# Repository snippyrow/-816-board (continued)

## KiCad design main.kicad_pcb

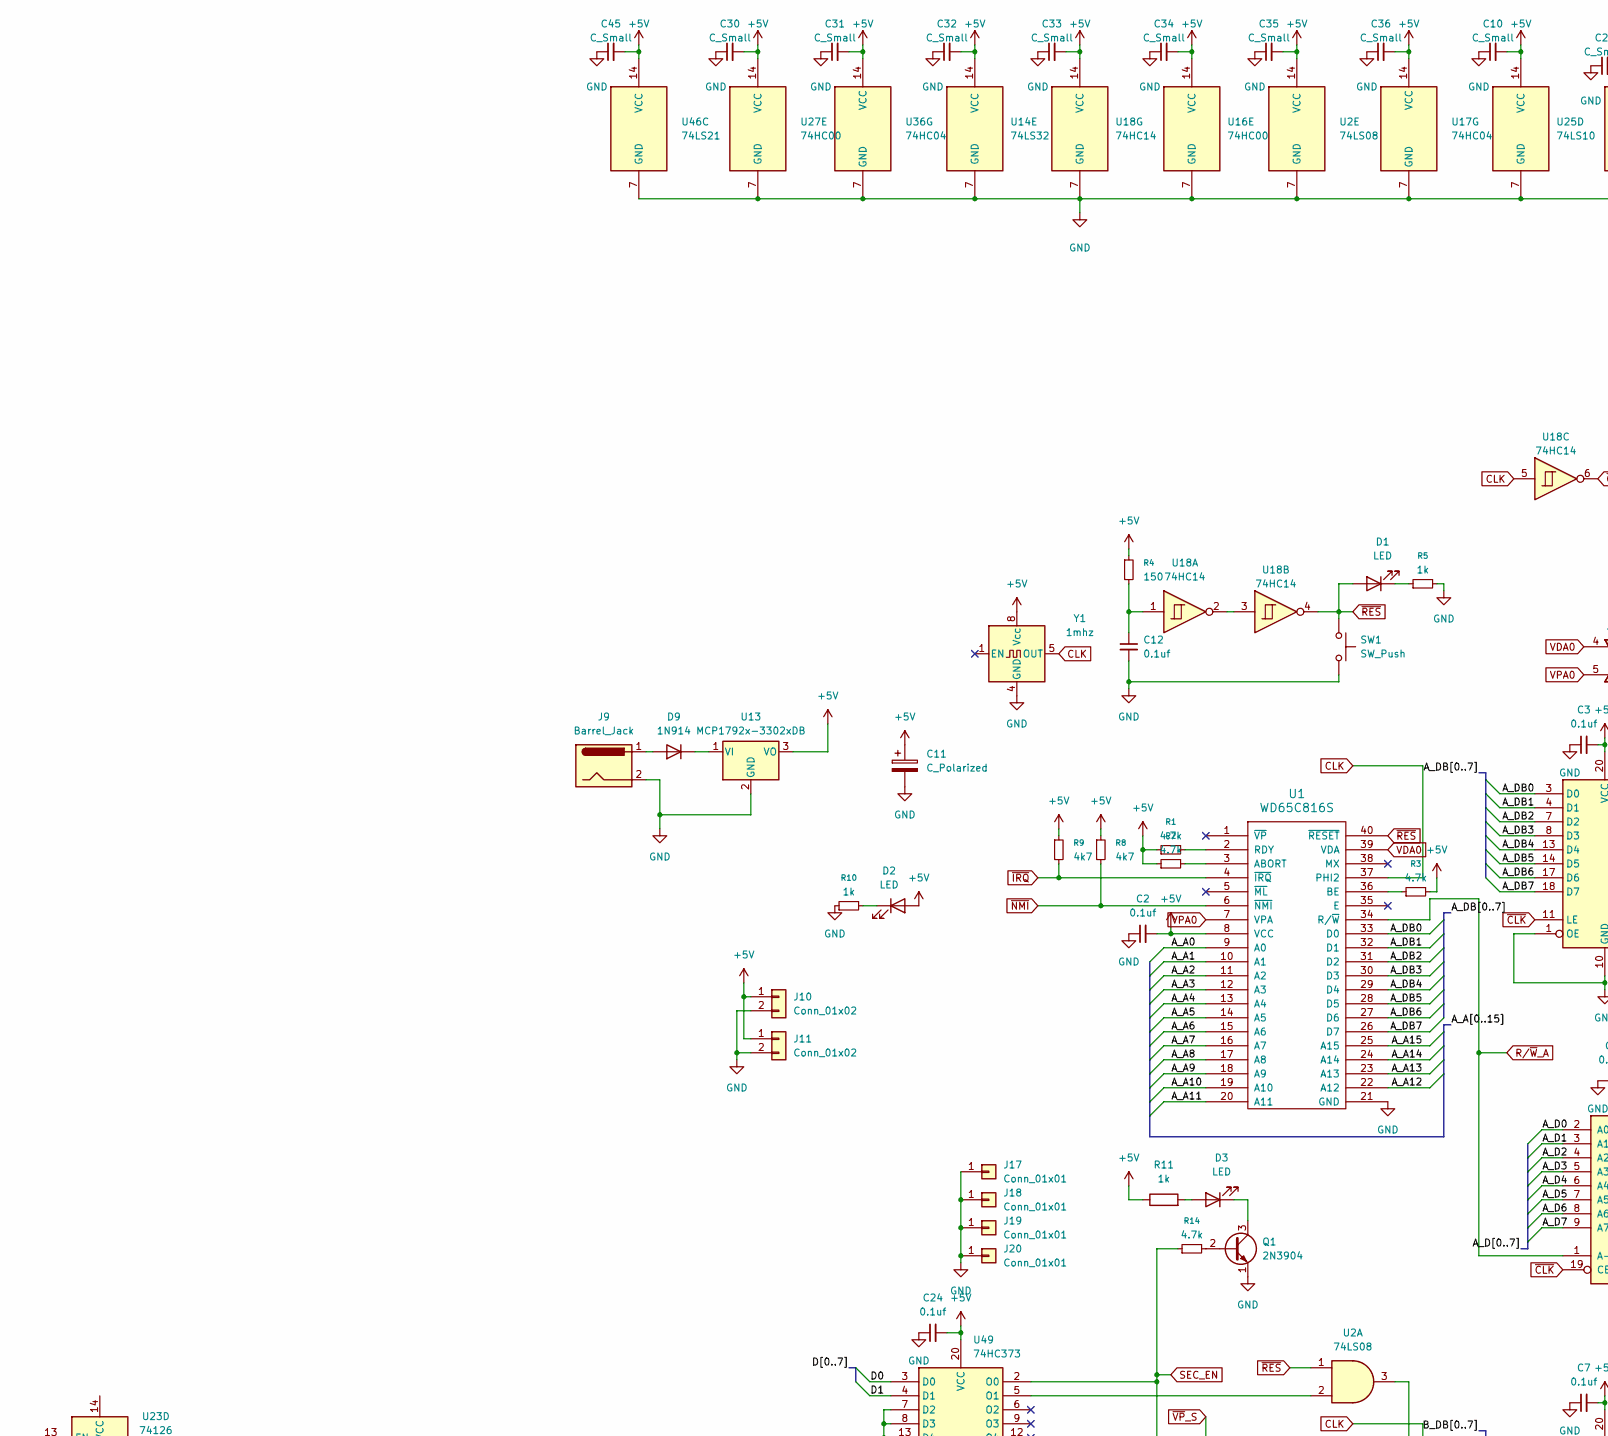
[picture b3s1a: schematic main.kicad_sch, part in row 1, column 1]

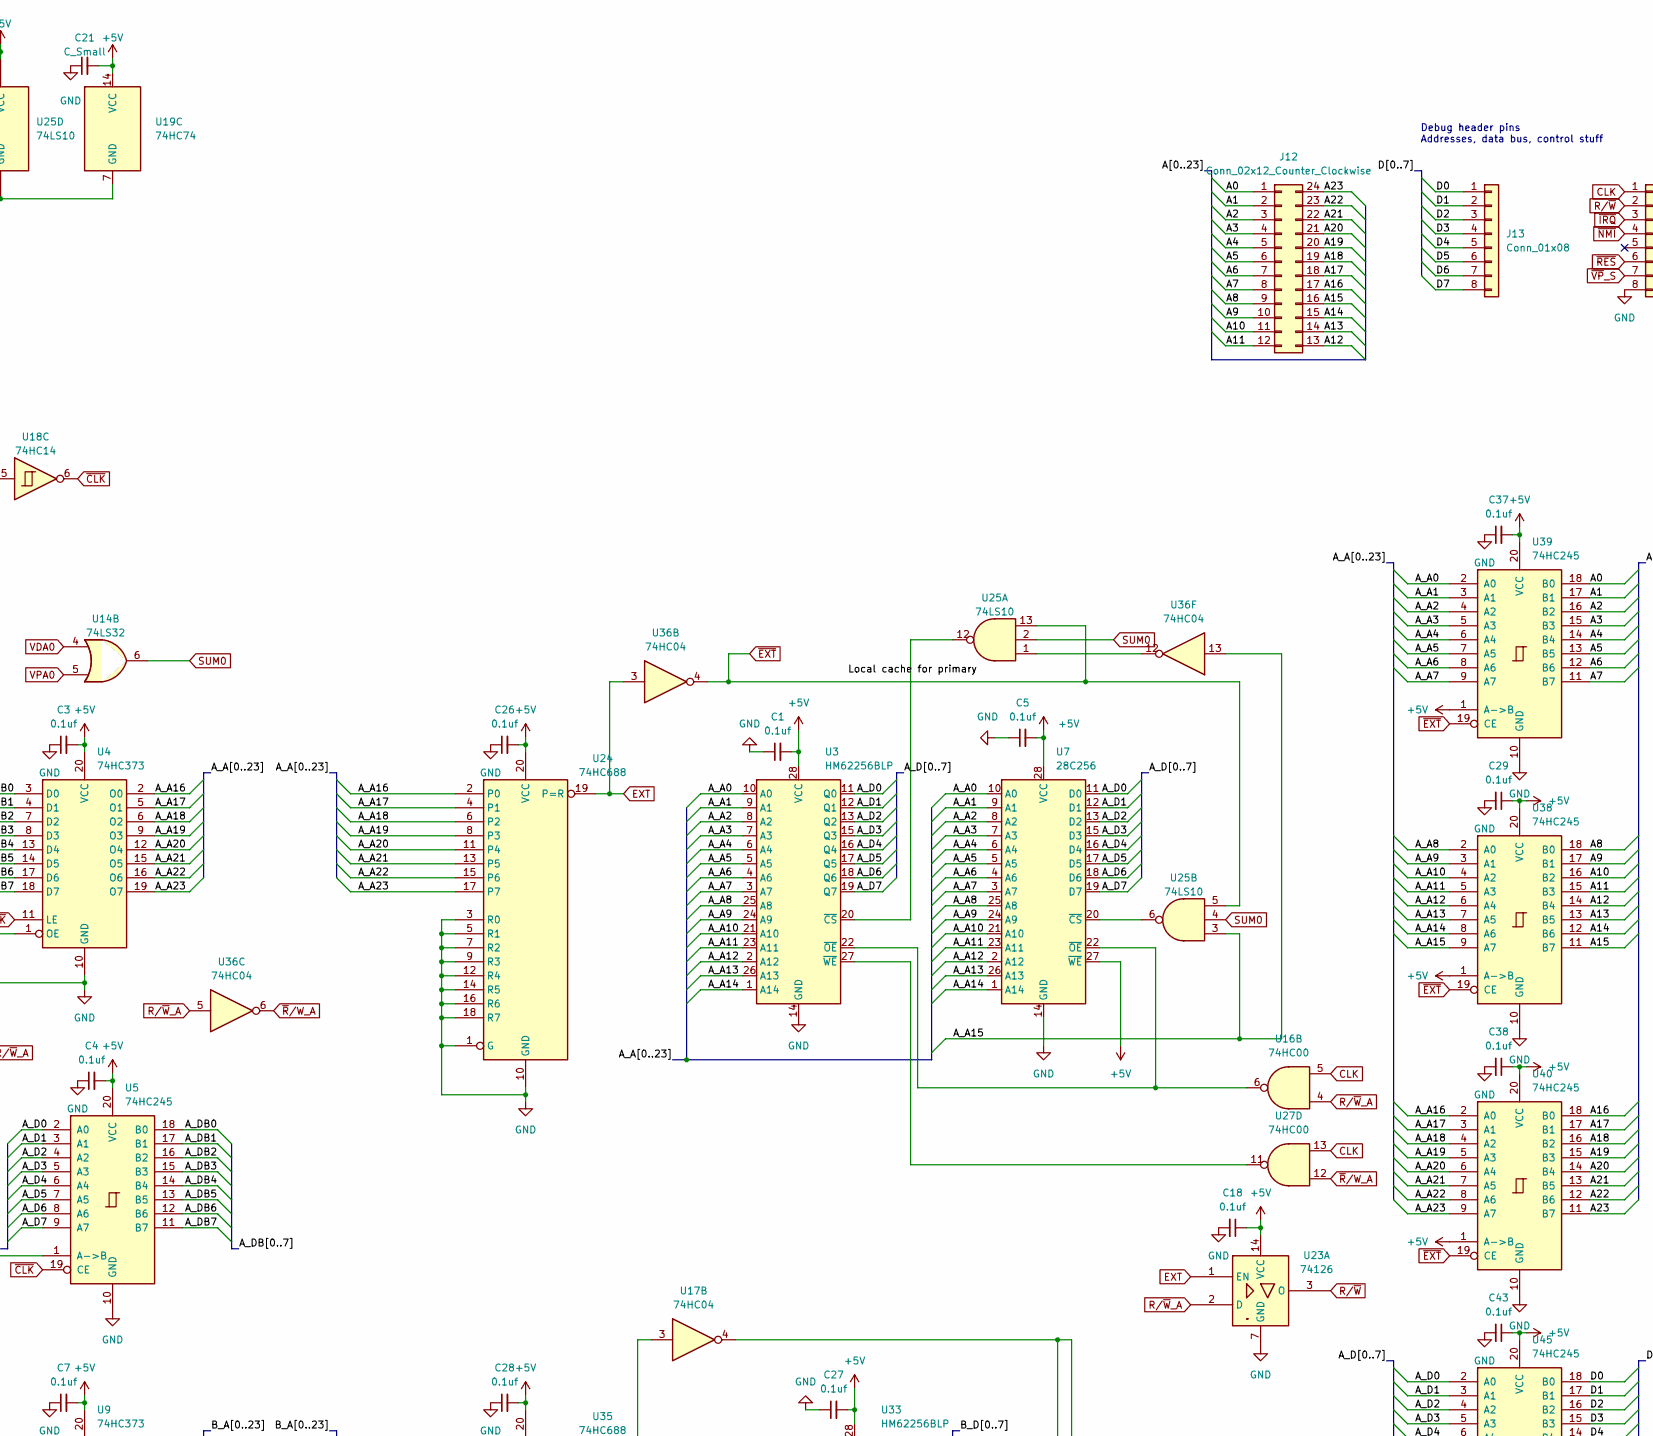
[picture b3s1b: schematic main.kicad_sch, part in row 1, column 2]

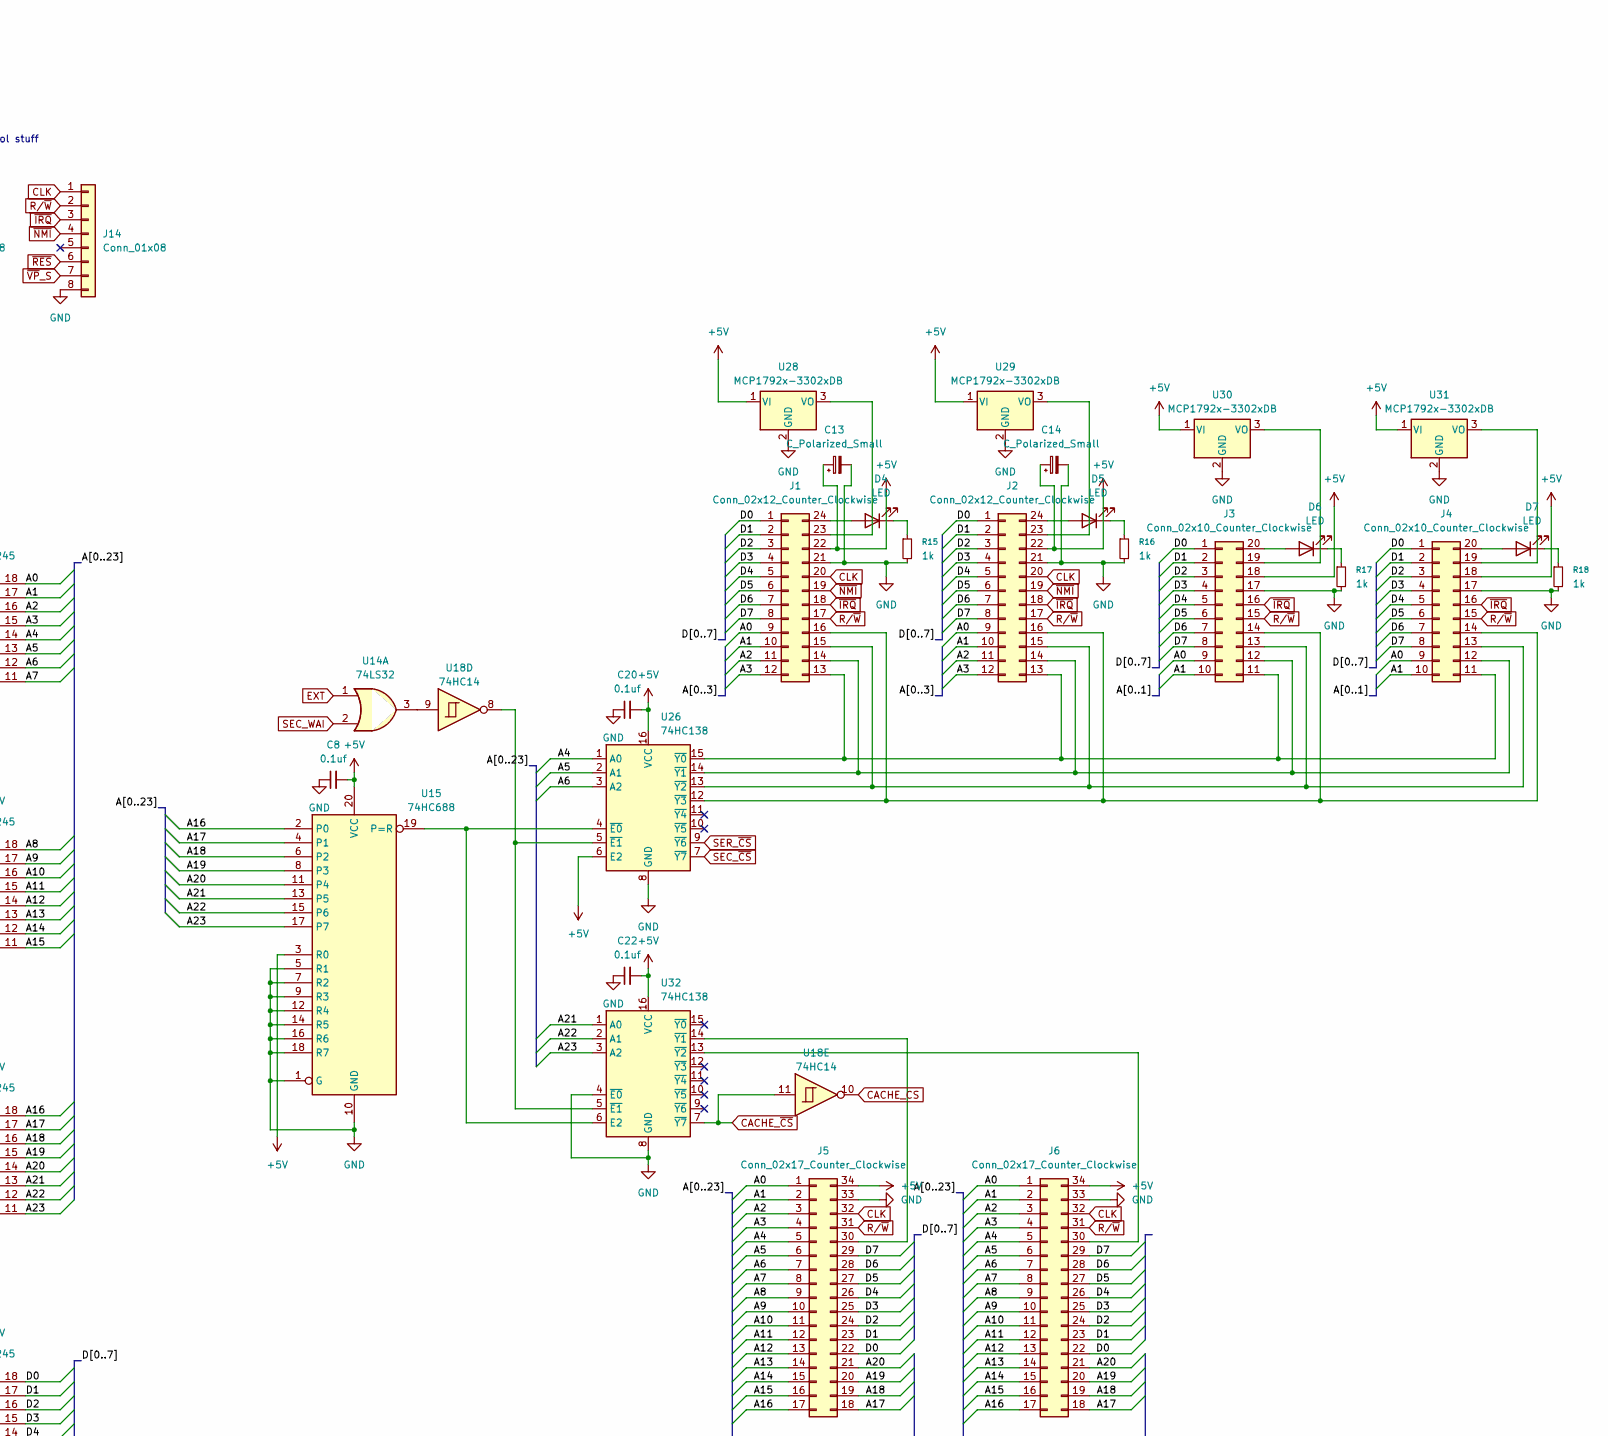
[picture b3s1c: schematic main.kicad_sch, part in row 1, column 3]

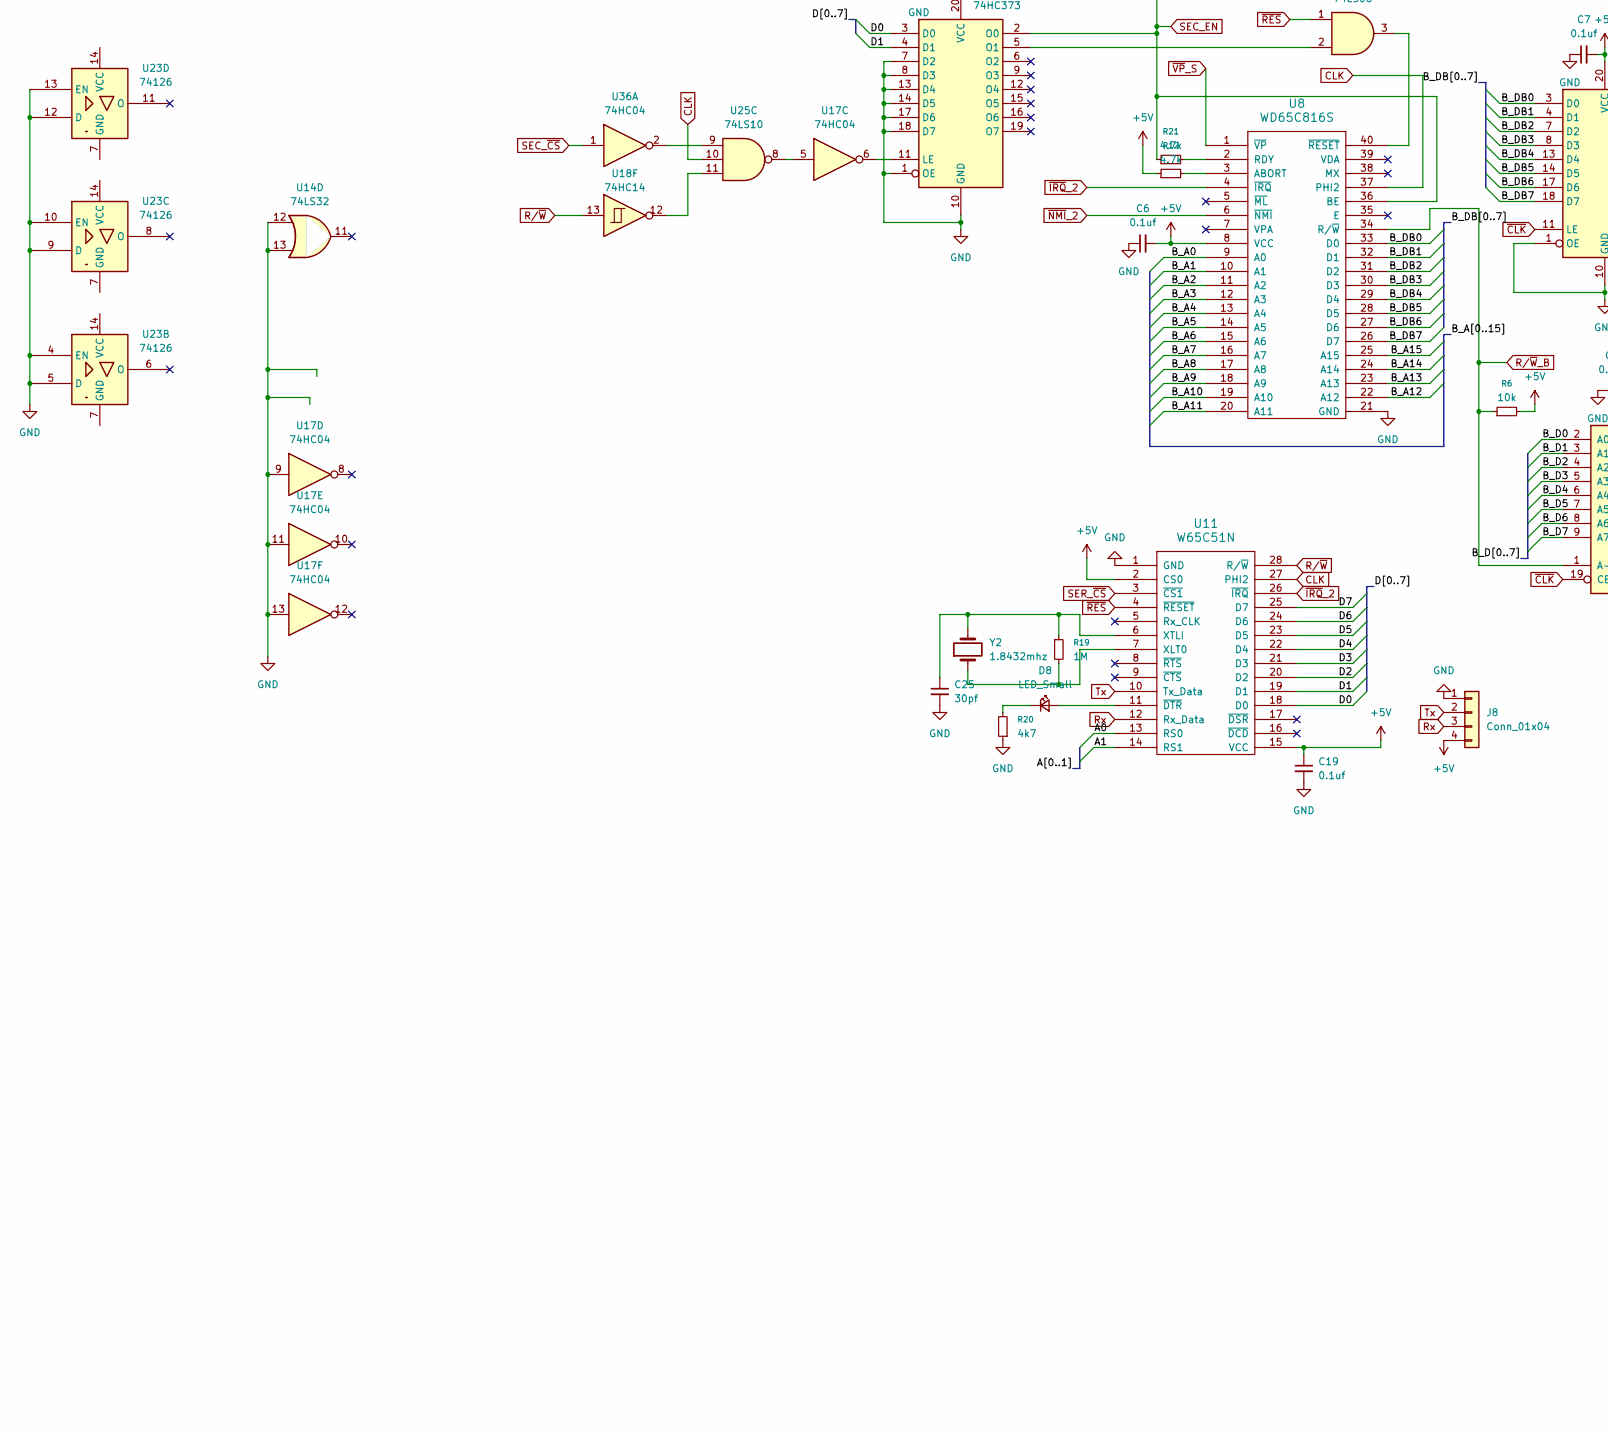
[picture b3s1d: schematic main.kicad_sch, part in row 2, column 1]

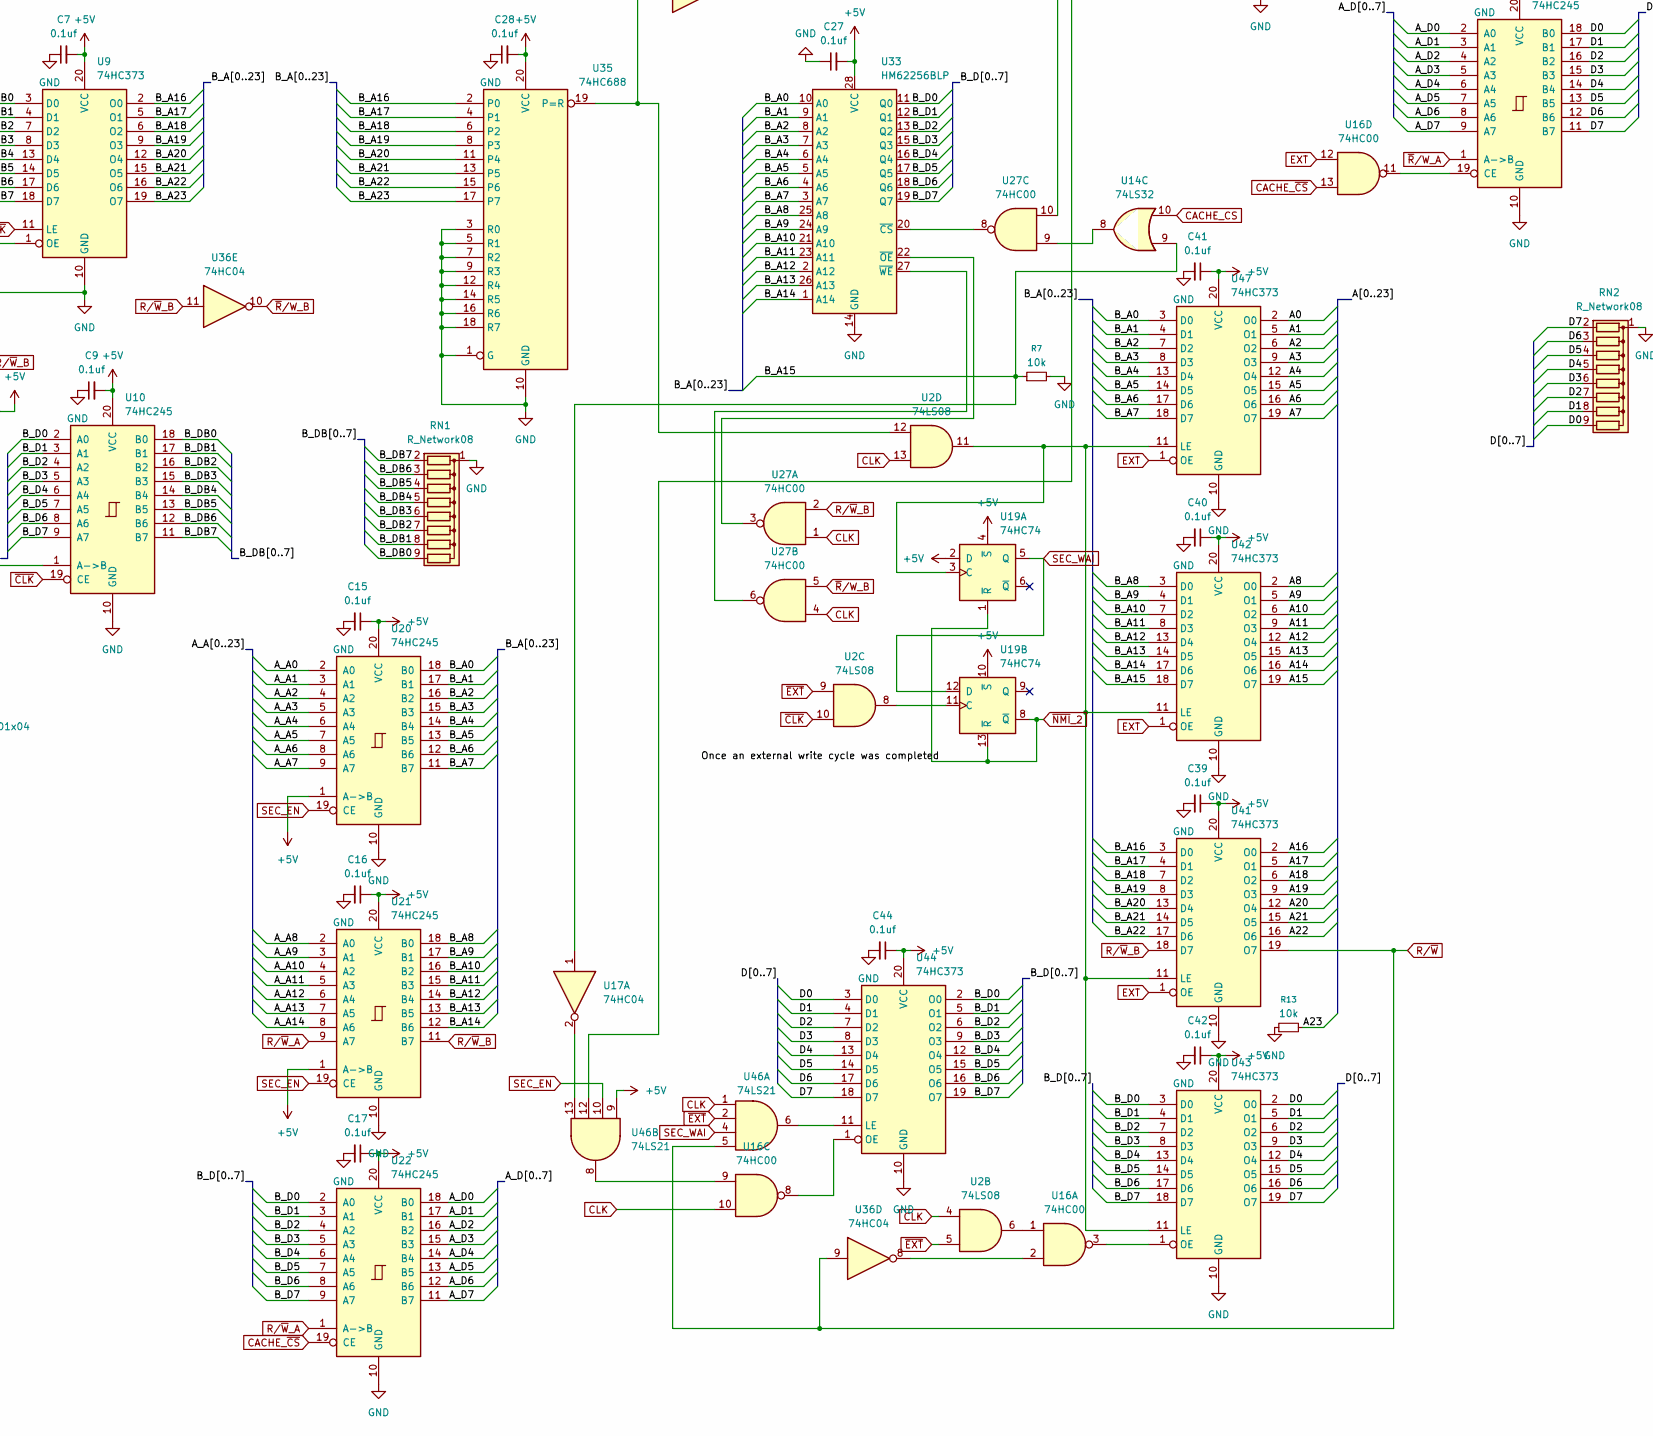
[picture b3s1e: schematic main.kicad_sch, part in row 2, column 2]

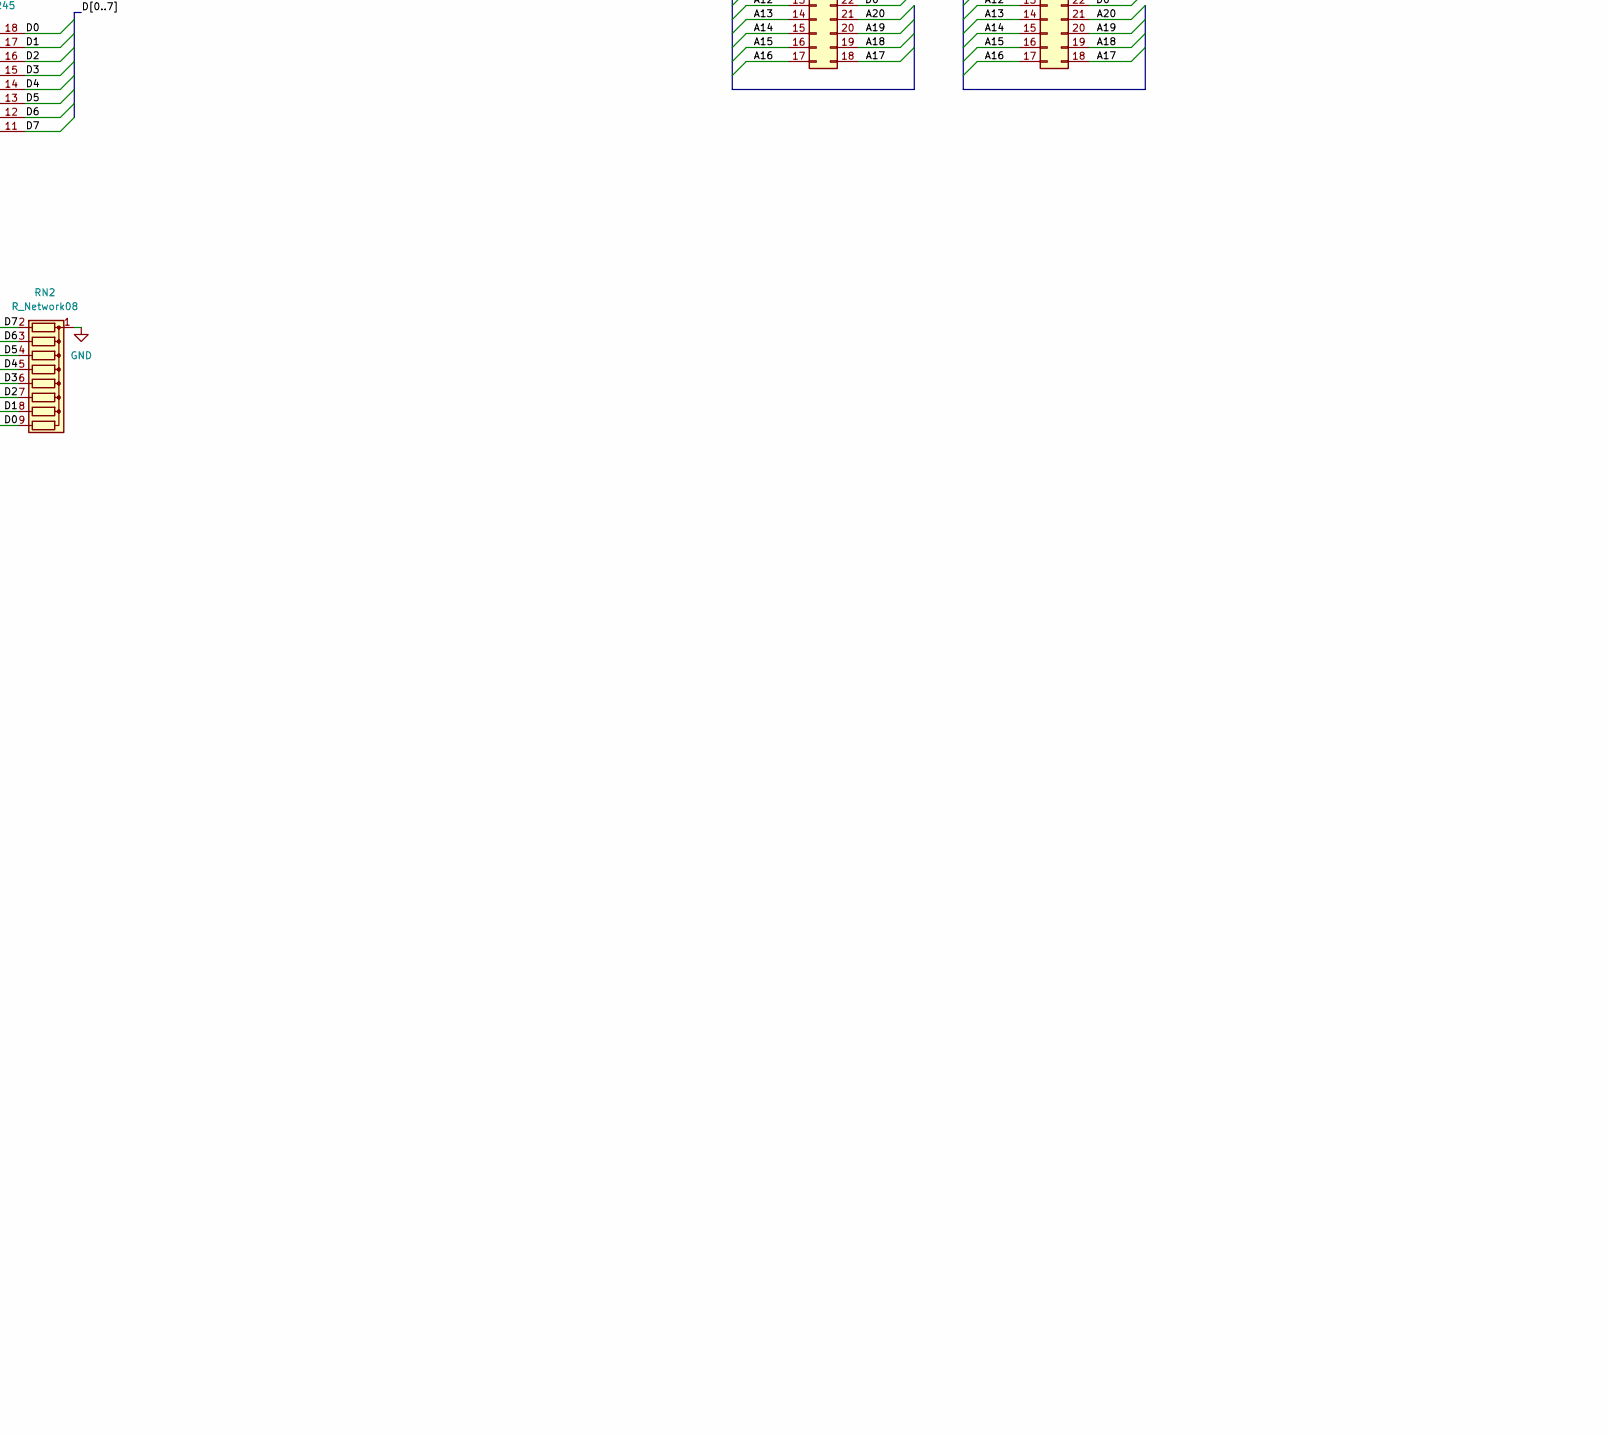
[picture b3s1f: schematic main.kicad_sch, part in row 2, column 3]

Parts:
C1, C2, C3, C4, C5, C6, C7, C8, C9, C12, C15, C16, C17, C18, C19, C20, C22, C24, C26, C27, C28, C29, C37, C38, C39, C40, C41, C42, C43, C44: 0.1uf; C_1206_3216Metric
C10, C21, C30, C31, C32, C33, C34, C35, C36, C45: C_Small; C_1206_3216Metric
C11: C_Polarized; CP_Radial_D10.0mm_P3.50mm
C13, C14: C_Polarized_Small; CP_Radial_D5.0mm_P2.00mm
C25: 30pf; C_Disc_D3.0mm_W2.0mm_P2.50mm
D1, D2, D3: LED; LED_D3.0mm
D4, D5, D6, D7: LED; LED_1206_3216Metric
D8: LED_Small; LED_1206_3216Metric_Pad1.42x1.75mm_HandSolder
D9: 1N914; D_1206_3216Metric_Pad1.42x1.75mm_HandSolder
J1, J2: Conn_02x12_Counter_Clockwise; AliExpress_24
J3, J4: Conn_02x10_Counter_Clockwise; AliExpress_20
J5, J6: Conn_02x17_Counter_Clockwise; AliExpress_36
J8: Conn_01x04; PinSocket_1x04_P2.54mm_Vertical
J9: Barrel_Jack; BarrelJack_Horizontal
J10, J11: Conn_01x02; PinHeader_1x02_P2.54mm_Vertical
J12: Conn_02x12_Counter_Clockwise; PinSocket_2x12_P2.54mm_Vertical
J13, J14: Conn_01x08; PinSocket_1x08_P2.54mm_Vertical
J17, J18, J19, J20: Conn_01x01; MountingHole_3mm_Pad
Q1: 2N3904; TO-92_Inline
R1, R2, R3, R12, R14, R21: 4.7k; R_1206_3216Metric_Pad1.30x1.75mm_HandSolder
R4: 150; R_Axial_DIN0204_L3.6mm_D1.6mm_P7.62mm_Horizontal
R5, R10, R11, R15, R16, R17, R18: 1k; R_1206_3216Metric_Pad1.30x1.75mm_HandSolder
R6, R7, R13: 10k; R_1206_3216Metric_Pad1.30x1.75mm_HandSolder
R8, R9, R20: 4k7; R_1206_3216Metric_Pad1.30x1.75mm_HandSolder
R19: 1M; R_Axial_DIN0207_L6.3mm_D2.5mm_P7.62mm_Horizontal
RN1, RN2: R_Network08; R_Array_SIP9
SW1: SW_Push; SW_PUSH_6mm
U1, U8: WD65C816S; DIP-40_W15.24mm_Socket
U2: 74LS08; DIP-14_W7.62mm_Socket
U3, U33: HM62256BLP; DIP-28_W15.24mm_Socket
U4, U9, U41, U42, U43, U44, U47, U49: 74HC373; DIP-20_W7.62mm_Socket
U5, U10, U20, U21, U22, U38, U39, U40, U45: 74HC245; DIP-20_W7.62mm_Socket
U7: 28C256; DIP_Socket-28_W11.9_W12.7_W15.24_W17.78_W18.5_3M_228-1277-0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
U11: W65C51N; DIP-28_W15.24mm_Socket
U13, U28, U29, U30, U31: MCP1792x-3302xDB; SOT-89-3_Handsoldering
U14: 74LS32; DIP-14_W7.62mm_Socket
U15, U24, U35: 74HC688; DIP-20_W7.62mm_Socket
U16, U27: 74HC00; DIP-14_W7.62mm_Socket
U17, U36: 74HC04; DIP-14_W7.62mm_Socket
U18: 74HC14; DIP-14_W7.62mm_Socket
U19: 74HC74; DIP-14_W7.62mm_Socket
U23: 74126; DIP-14_W7.62mm_Socket
U25: 74LS10; DIP-14_W7.62mm_Socket
U26, U32: 74HC138; DIP-16_W7.62mm_Socket
U46: 74LS21; DIP-14_W7.62mm_Socket
Y1: 1mhz; Oscillator_DIP-8
Y2: 1.8432mhz; Crystal_HC52-6mm_Vertical

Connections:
+5V: C1.2, C2.2, C3.2, C4.2, C5.2, C6.2, C7.2, C8.2, C9.2, C10.2, C11.1, C13.1, C14.1, C15.1, C16.1, C17.1, C18.1, C19.1, C20.2, C21.2, C22.2, C24.2, C26.2, C27.2, C28.2, C29.1, C30.2, C31.2, C32.2, C33.2, C34.2, C35.2, C36.2, C37.2, C38.1, C39.1, C40.1, C41.1, C42.1, C43.1, C44.1, C45.2, D2.2 (A), J1.22, J2.22, J3.18, J4.18, J5.34, J6.34, J8.4, J10.1, J11.1, R1.1, R2.1, R3.2, R4.1, R6.2, R8.1, R9.1, R11.1, R12.1, U1.8 (VCC), U2.14 (VCC), U3.28 (VCC), U4.20 (VCC), U5.20 (VCC), U7.27 (~WE), U7.28 (VCC), U8.8 (VCC), U9.20 (VCC), U10.20 (VCC), U11.2 (CS0), U11.15 (VCC), U13.3 (VO), U14.14 (VCC), U15.3 (R0), U15.20 (VCC), U16.14 (VCC), U17.14 (VCC), U18.14 (VCC), U19.2 (D), U19.4 (~S), U19.10 (~S), U19.14 (VCC), U20.1 (A->B), U20.20 (VCC), U21.1 (A->B), U21.20 (VCC), U22.20 (VCC), U23.14 (VCC), U24.20 (VCC), U25.14 (VCC), U26.6 (E2), U26.16 (VCC), U27.14 (VCC), U28.1 (VI), U29.1 (VI), U30.1 (VI), U31.1 (VI), U32.16 (VCC), U33.28 (VCC), U35.20 (VCC), U36.14 (VCC), U38.1 (A->B), U38.20 (VCC), U39.1 (A->B), U39.20 (VCC), U40.1 (A->B), U40.20 (VCC), U41.20 (VCC), U42.20 (VCC), U43.20 (VCC), U44.20 (VCC), U45.20 (VCC), U46.9, U46.14 (VCC), U47.20 (VCC), U49.20 (VCC), Y1.8 (Vcc)
/A0: J1.9, J2.9, J3.9, J4.9, J5.1, J6.1, J12.1, U11.13 (RS0), U39.18 (B0), U47.2 (O0)
/A1: J1.10, J2.10, J3.10, J4.10, J5.2, J6.2, J12.2, U11.14 (RS1), U39.17 (B1), U47.5 (O1)
/A2: J1.11, J2.11, J5.3, J6.3, J12.3, U39.16 (B2), U47.6 (O2)
/A3: J1.12, J2.12, J5.4, J6.4, J12.4, U39.15 (B3), U47.9 (O3)
/A4: J5.5, J6.5, J12.5, U26.1 (A0), U39.14 (B4), U47.12 (O4)
/A5: J5.6, J6.6, J12.6, U26.2 (A1), U39.13 (B5), U47.15 (O5)
/A6: J5.7, J6.7, J12.7, U26.3 (A2), U39.12 (B6), U47.16 (O6)
/A7: J5.8, J6.8, J12.8, U39.11 (B7), U47.19 (O7)
/A8: J5.9, J6.9, J12.9, U38.18 (B0), U42.2 (O0)
/A9: J5.10, J6.10, J12.10, U38.17 (B1), U42.5 (O1)
/A10: J5.11, J6.11, J12.11, U38.16 (B2), U42.6 (O2)
/A11: J5.12, J6.12, J12.12, U38.15 (B3), U42.9 (O3)
/A12: J5.13, J6.13, J12.13, U38.14 (B4), U42.12 (O4)
/A13: J5.14, J6.14, J12.14, U38.13 (B5), U42.15 (O5)
/A14: J5.15, J6.15, J12.15, U38.12 (B6), U42.16 (O6)
/A15: J5.16, J6.16, J12.16, U38.11 (B7), U42.19 (O7)
/A16: J5.17, J6.17, J12.17, U15.2 (P0), U40.18 (B0), U41.2 (O0)
/A17: J5.18, J6.18, J12.18, U15.4 (P1), U40.17 (B1), U41.5 (O1)
/A18: J5.19, J6.19, J12.19, U15.6 (P2), U40.16 (B2), U41.6 (O2)
/A19: J5.20, J6.20, J12.20, U15.8 (P3), U40.15 (B3), U41.9 (O3)
/A20: J5.21, J6.21, J12.21, U15.11 (P4), U40.14 (B4), U41.12 (O4)
/A21: J12.22, U15.13 (P5), U32.1 (A0), U40.13 (B5), U41.15 (O5)
/A22: J12.23, U15.15 (P6), U32.2 (A1), U40.12 (B6), U41.16 (O6)
/A23: J12.24, R13.2, U15.17 (P7), U32.3 (A2), U40.11 (B7)
/A_A0: U1.9 (A0), U3.10 (A0), U7.10 (A0), U20.2 (A0), U39.2 (A0)
/A_A1: U1.10 (A1), U3.9 (A1), U7.9 (A1), U20.3 (A1), U39.3 (A1)
/A_A2: U1.11 (A2), U3.8 (A2), U7.8 (A2), U20.4 (A2), U39.4 (A2)
/A_A3: U1.12 (A3), U3.7 (A3), U7.7 (A3), U20.5 (A3), U39.5 (A3)
/A_A4: U1.13 (A4), U3.6 (A4), U7.6 (A4), U20.6 (A4), U39.6 (A4)
/A_A5: U1.14 (A5), U3.5 (A5), U7.5 (A5), U20.7 (A5), U39.7 (A5)
/A_A6: U1.15 (A6), U3.4 (A6), U7.4 (A6), U20.8 (A6), U39.8 (A6)
/A_A7: U1.16 (A7), U3.3 (A7), U7.3 (A7), U20.9 (A7), U39.9 (A7)
/A_A8: U1.17 (A8), U3.25 (A8), U7.25 (A8), U21.2 (A0), U38.2 (A0)
/A_A9: U1.18 (A9), U3.24 (A9), U7.24 (A9), U21.3 (A1), U38.3 (A1)
/A_A10: U1.19 (A10), U3.21 (A10), U7.21 (A10), U21.4 (A2), U38.4 (A2)
/A_A11: U1.20 (A11), U3.23 (A11), U7.23 (A11), U21.5 (A3), U38.5 (A3)
/A_A12: U1.22 (A12), U3.2 (A12), U7.2 (A12), U21.6 (A4), U38.6 (A4)
/A_A13: U1.23 (A13), U3.26 (A13), U7.26 (A13), U21.7 (A5), U38.7 (A5)
/A_A14: U1.24 (A14), U3.1 (A14), U7.1 (A14), U21.8 (A6), U38.8 (A6)
/A_A15: U1.25 (A15), U25.3, U36.13, U38.9 (A7)
/A_A16: U4.2 (O0), U24.2 (P0), U40.2 (A0)
/A_A17: U4.5 (O1), U24.4 (P1), U40.3 (A1)
/A_A18: U4.6 (O2), U24.6 (P2), U40.4 (A2)
/A_A19: U4.9 (O3), U24.8 (P3), U40.5 (A3)
/A_A20: U4.12 (O4), U24.11 (P4), U40.6 (A4)
/A_A21: U4.15 (O5), U24.13 (P5), U40.7 (A5)
/A_A22: U4.16 (O6), U24.15 (P6), U40.8 (A6)
/A_A23: U4.19 (O7), U24.17 (P7), U40.9 (A7)
/A_D0: U3.11 (Q0), U5.2 (A0), U7.11 (D0), U22.18 (B0), U45.2 (A0)
/A_D1: U3.12 (Q1), U5.3 (A1), U7.12 (D1), U22.17 (B1), U45.3 (A1)
/A_D2: U3.13 (Q2), U5.4 (A2), U7.13 (D2), U22.16 (B2), U45.4 (A2)
/A_D3: U3.15 (Q3), U5.5 (A3), U7.15 (D3), U22.15 (B3), U45.5 (A3)
/A_D4: U3.16 (Q4), U5.6 (A4), U7.16 (D4), U22.14 (B4), U45.6 (A4)
/A_D5: U3.17 (Q5), U5.7 (A5), U7.17 (D5), U22.13 (B5), U45.7 (A5)
/A_D6: U3.18 (Q6), U5.8 (A6), U7.18 (D6), U22.12 (B6), U45.8 (A6)
/A_D7: U3.19 (Q7), U5.9 (A7), U7.19 (D7), U22.11 (B7), U45.9 (A7)
/A_DB0: U1.33 (D0), U4.3 (D0), U5.18 (B0)
/A_DB1: U1.32 (D1), U4.4 (D1), U5.17 (B1)
/A_DB2: U1.31 (D2), U4.7 (D2), U5.16 (B2)
/A_DB3: U1.30 (D3), U4.8 (D3), U5.15 (B3)
/A_DB4: U1.29 (D4), U4.13 (D4), U5.14 (B4)
/A_DB5: U1.28 (D5), U4.14 (D5), U5.13 (B5)
/A_DB6: U1.27 (D6), U4.17 (D6), U5.12 (B6)
/A_DB7: U1.26 (D7), U4.18 (D7), U5.11 (B7)
/B_A0: U8.9 (A0), U20.18 (B0), U33.10 (A0), U47.3 (D0)
/B_A1: U8.10 (A1), U20.17 (B1), U33.9 (A1), U47.4 (D1)
/B_A2: U8.11 (A2), U20.16 (B2), U33.8 (A2), U47.7 (D2)
/B_A3: U8.12 (A3), U20.15 (B3), U33.7 (A3), U47.8 (D3)
/B_A4: U8.13 (A4), U20.14 (B4), U33.6 (A4), U47.13 (D4)
/B_A5: U8.14 (A5), U20.13 (B5), U33.5 (A5), U47.14 (D5)
/B_A6: U8.15 (A6), U20.12 (B6), U33.4 (A6), U47.17 (D6)
/B_A7: U8.16 (A7), U20.11 (B7), U33.3 (A7), U47.18 (D7)
/B_A8: U8.17 (A8), U21.18 (B0), U33.25 (A8), U42.3 (D0)
/B_A9: U8.18 (A9), U21.17 (B1), U33.24 (A9), U42.4 (D1)
/B_A10: U8.19 (A10), U21.16 (B2), U33.21 (A10), U42.7 (D2)
/B_A11: U8.20 (A11), U21.15 (B3), U33.23 (A11), U42.8 (D3)
/B_A12: U8.22 (A12), U21.14 (B4), U33.2 (A12), U42.13 (D4)
/B_A13: U8.23 (A13), U21.13 (B5), U33.26 (A13), U42.14 (D5)
/B_A14: U8.24 (A14), U21.12 (B6), U33.1 (A14), U42.17 (D6)
/B_A15: R7.1, U8.25 (A15), U14.9, U17.1, U42.18 (D7)
/B_A16: U9.2 (O0), U35.2 (P0), U41.3 (D0)
/B_A17: U9.5 (O1), U35.4 (P1), U41.4 (D1)
/B_A18: U9.6 (O2), U35.6 (P2), U41.7 (D2)
/B_A19: U9.9 (O3), U35.8 (P3), U41.8 (D3)
/B_A20: U9.12 (O4), U35.11 (P4), U41.13 (D4)
/B_A21: U9.15 (O5), U35.13 (P5), U41.14 (D5)
/B_A22: U9.16 (O6), U35.15 (P6), U41.17 (D6)
/B_A23: U9.19 (O7), U35.17 (P7)
/B_D0: U10.2 (A0), U22.2 (A0), U33.11 (Q0), U43.3 (D0), U44.2 (O0)
/B_D1: U10.3 (A1), U22.3 (A1), U33.12 (Q1), U43.4 (D1), U44.5 (O1)
/B_D2: U10.4 (A2), U22.4 (A2), U33.13 (Q2), U43.7 (D2), U44.6 (O2)
/B_D3: U10.5 (A3), U22.5 (A3), U33.15 (Q3), U43.8 (D3), U44.9 (O3)
/B_D4: U10.6 (A4), U22.6 (A4), U33.16 (Q4), U43.13 (D4), U44.12 (O4)
/B_D5: U10.7 (A5), U22.7 (A5), U33.17 (Q5), U43.14 (D5), U44.15 (O5)
/B_D6: U10.8 (A6), U22.8 (A6), U33.18 (Q6), U43.17 (D6), U44.16 (O6)
/B_D7: U10.9 (A7), U22.9 (A7), U33.19 (Q7), U43.18 (D7), U44.19 (O7)
/B_DB0: RN1.9 (R8), U8.33 (D0), U9.3 (D0), U10.18 (B0)
/B_DB1: RN1.8 (R7), U8.32 (D1), U9.4 (D1), U10.17 (B1)
/B_DB2: RN1.7 (R6), U8.31 (D2), U9.7 (D2), U10.16 (B2)
/B_DB3: RN1.6 (R5), U8.30 (D3), U9.8 (D3), U10.15 (B3)
/B_DB4: RN1.5 (R4), U8.29 (D4), U9.13 (D4), U10.14 (B4)
/B_DB5: RN1.4 (R3), U8.28 (D5), U9.14 (D5), U10.13 (B5)
/B_DB6: RN1.3 (R2), U8.27 (D6), U9.17 (D6), U10.12 (B6)
/B_DB7: RN1.2 (R1), U8.26 (D7), U9.18 (D7), U10.11 (B7)
/D0: J1.1, J2.1, J3.1, J4.1, J5.22, J6.22, J13.1, RN2.9 (R8), U11.18 (D0), U43.2 (O0), U44.3 (D0), U45.18 (B0), U49.3 (D0)
/D1: J1.2, J2.2, J3.2, J4.2, J5.23, J6.23, J13.2, RN2.8 (R7), U11.19 (D1), U43.5 (O1), U44.4 (D1), U45.17 (B1), U49.4 (D1)
/D2: J1.3, J2.3, J3.3, J4.3, J5.24, J6.24, J13.3, RN2.7 (R6), U11.20 (D2), U43.6 (O2), U44.7 (D2), U45.16 (B2)
/D3: J1.4, J2.4, J3.4, J4.4, J5.25, J6.25, J13.4, RN2.6 (R5), U11.21 (D3), U43.9 (O3), U44.8 (D3), U45.15 (B3)
/D4: J1.5, J2.5, J3.5, J4.5, J5.26, J6.26, J13.5, RN2.5 (R4), U11.22 (D4), U43.12 (O4), U44.13 (D4), U45.14 (B4)
/D5: J1.6, J2.6, J3.6, J4.6, J5.27, J6.27, J13.6, RN2.4 (R3), U11.23 (D5), U43.15 (O5), U44.14 (D5), U45.13 (B5)
/D6: J1.7, J2.7, J3.7, J4.7, J5.28, J6.28, J13.7, RN2.3 (R2), U11.24 (D6), U43.16 (O6), U44.17 (D6), U45.12 (B6)
/D7: J1.8, J2.8, J3.8, J4.8, J5.29, J6.29, J13.8, RN2.2 (R1), U11.25 (D7), U43.19 (O7), U44.18 (D7), U45.11 (B7)
CACHE_CS: U14.10, U18.10
CACHE_~CS: U16.13, U18.11, U22.19 (CE), U32.7 (~Y7)
CLK: J1.20, J2.20, J5.32, J6.32, J14.1, U1.37 (PHI2), U2.4, U2.13, U8.37 (PHI2), U11.27 (PHI2), U16.5, U16.10, U18.5, U25.10, U27.1, U27.4, U27.13, U46.1, Y1.5 (OUT)
EXT: U14.1, U16.12, U23.1 (EN), U24.19 (P=R), U36.3, U41.1 (OE), U42.1 (OE), U47.1 (OE)
GND: C1.1, C2.1, C3.1, C4.1, C5.1, C6.1, C7.1, C8.1, C9.1, C10.1, C11.2, C12.2, C13.2, C14.2, C15.2, C16.2, C17.2, C18.2, C19.2, C20.1, C21.1, C22.1, C24.1, C25.2, C26.1, C27.1, C28.1, C29.2, C30.1, C31.1, C32.1, C33.1, C34.1, C35.1, C36.1, C37.1, C38.2, C39.2, C40.2, C41.2, C42.2, C43.2, C44.2, C45.1, J1.21, J2.21, J3.17, J4.17, J5.33, J6.33, J8.1, J9.2, J10.2, J11.2, J14.8, J17.1, J18.1, J19.1, J20.1, Q1.1 (E), R5.2, R7.2, R10.1, R13.1, R15.2, R16.2, R17.2, R18.2, R20.1, RN1.1 (common), RN2.1 (common), SW1.2, U1.21 (GND), U2.7 (GND), U3.14 (GND), U4.1 (OE), U4.10 (GND), U5.10 (GND), U7.14 (GND), U8.21 (GND), U9.1 (OE), U9.10 (GND), U10.10 (GND), U11.1 (GND), U13.2 (GND), U14.7 (GND), U14.12, U14.13, U15.1 (G), U15.5 (R1), U15.7 (R2), U15.9 (R3), U15.10 (GND), U15.12 (R4), U15.14 (R5), U15.16 (R6), U15.18 (R7), U16.7 (GND), U17.7 (GND), U17.9, U17.11, U17.13, U18.7 (GND), U19.7 (GND), U20.10 (GND), U21.10 (GND), U22.10 (GND), U23.4 (EN), U23.5 (D), U23.7 (GND), U23.9 (D), U23.10 (EN), U23.12 (D), U23.13 (EN), U24.1 (G), U24.3 (R0), U24.5 (R1), U24.7 (R2), U24.9 (R3), U24.10 (GND), U24.12 (R4), U24.14 (R5), U24.16 (R6), U24.18 (R7), U25.7 (GND), U26.8 (GND), U27.7 (GND), U28.2 (GND), U29.2 (GND), U30.2 (GND), U31.2 (GND), U32.4 (~E0), U32.8 (GND), U33.14 (GND), U35.1 (G), U35.3 (R0), U35.5 (R1), U35.7 (R2), U35.9 (R3), U35.10 (GND), U35.12 (R4), U35.14 (R5), U35.16 (R6), U35.18 (R7), U36.7 (GND), U38.10 (GND), U39.10 (GND), U40.10 (GND), U41.10 (GND), U42.10 (GND), U43.10 (GND), U44.10 (GND), U45.10 (GND), U46.7 (GND), U47.10 (GND), U49.1 (OE), U49.7 (D2), U49.8 (D3), U49.10 (GND), U49.13 (D4), U49.14 (D5), U49.17 (D6), U49.18 (D7), Y1.4 (GND)
unnamed: C12.1, R4.2, U18.1
unnamed: D1.1 (K), R5.1
unnamed: D2.1 (K), R10.2
unnamed: D3.2 (A), R11.2
unnamed: D3.1 (K), Q1.3 (C)
unnamed: D4.2 (A), J1.24
unnamed: D4.1 (K), R15.1
unnamed: D5.2 (A), J2.24
unnamed: D5.1 (K), R16.1
unnamed: D6.2 (A), J3.20
unnamed: D6.1 (K), R17.1
unnamed: D7.2 (A), J4.20
unnamed: D7.1 (K), R18.1
unnamed: D8.2 (A), U11.11 (~DTR)
unnamed: D8.1 (K), R20.2
unnamed: D9.2 (A), J9.1
unnamed: D9.1 (K), U13.1 (VI)
unnamed: J1.13, J2.13, J3.11, J4.11, U26.15 (~Y0)
unnamed: J1.14, J2.14, J3.12, J4.12, U26.14 (~Y1)
unnamed: J1.15, J2.15, J3.13, J4.13, U26.13 (~Y2)
unnamed: J1.16, J2.16, J3.14, J4.14, U26.12 (~Y3)
unnamed: J1.23, U28.3 (VO)
unnamed: J2.23, U29.3 (VO)
unnamed: J3.19, U30.3 (VO)
unnamed: J4.19, U31.3 (VO)
unnamed: J5.30, U32.14 (~Y1)
unnamed: J6.30, U32.13 (~Y2)
unnamed: Q1.2 (B), R14.2
unnamed: R2.2, U1.3 (ABORT)
unnamed: R3.1, U1.36 (BE)
unnamed: R1.2, U1.2 (RDY)
unnamed: U3.20 (~CS), U25.12
unnamed: U3.22 (~OE), U7.22 (~OE), U16.6
unnamed: U3.27 (~WE), U27.11
unnamed: U7.20 (~CS), U25.6
unnamed: R12.2, U8.3 (ABORT)
unnamed: R21.2, U8.2 (RDY)
unnamed: U2.3, U8.40 (~RESET)
unnamed: R19.2, U11.7 (XLT0), Y2.1
unnamed: C25.1, R19.1, U11.6 (XTLI), Y2.2
unnamed: U14.3, U18.9
unnamed: U14.8, U27.9
unnamed: U15.19 (P=R), U26.4 (~E0), U32.6 (E2)
unnamed: U2.6, U16.1
unnamed: U16.2, U36.8
unnamed: U16.9, U46.8
unnamed: U17.2, U46.13
unnamed: U17.4, U27.10, U46.12
unnamed: U17.5, U25.8
unnamed: U18.2, U18.3
unnamed: U18.12, U25.11
unnamed: U2.11, U19.3 (C), U41.11 (LE), U42.11 (LE), U43.11 (LE), U47.11 (LE)
unnamed: U2.8, U19.11 (C)
unnamed: U25.1, U36.12
unnamed: U25.9, U36.2
unnamed: U18.8, U26.5 (~E1), U32.5 (~E1)
unnamed: U27.8, U33.20 (~CS)
unnamed: U27.3, U33.22 (~OE)
unnamed: U27.6, U33.27 (~WE)
unnamed: U2.12, U17.3, U35.19 (P=R)
unnamed: U16.3, U43.1 (OE)
unnamed: U44.11 (LE), U46.6
unnamed: U16.8, U44.1 (OE)
unnamed: U16.11, U45.19 (CE)
unnamed: U17.6, U49.11 (LE)
unnamed: U2.2, U49.5 (O1)
Rx: J8.3, U11.12 (Rx_Data)
R/~W: J1.17, J2.17, J3.15, J4.15, J5.31, J6.31, J14.2, U11.28 (R/~W), U18.13, U23.3 (O), U36.9, U41.19 (O7), U46.5
R/~W_A: U1.34 (R/~W), U5.1 (A->B), U16.4, U21.9 (A7), U22.1 (A->B), U23.2 (D), U36.5
R/~W_B: R6.1, U8.34 (R/~W), U10.1 (A->B), U21.11 (B7), U27.2, U36.11, U41.18 (D7)
SEC_EN: R14.1, R21.1, U8.36 (BE), U20.19 (CE), U21.19 (CE), U46.10, U49.2 (O0)
SEC_WAI: U14.2, U19.5 (Q), U19.12 (D), U46.4
SEC_~CS: U26.7 (~Y7), U36.1
SER_~CS: U11.3 (~CS1), U26.9 (~Y6)
SUM0: U14.6, U25.2, U25.4
Tx: J8.2, U11.10 (Tx_Data)
VDA0: U1.39 (VDA), U14.4
VPA0: U1.7 (VPA), U14.5
~CLK: U2.10, U4.11 (LE), U5.19 (CE), U9.11 (LE), U10.19 (CE), U18.6
~EXT: U2.5, U2.9, U25.5, U25.13, U36.4, U38.19 (CE), U39.19 (CE), U40.19 (CE), U46.2
~IRQ: J1.18, J2.18, J3.16, J4.16, J14.3, R9.2, U1.4 (~IRQ)
~IRQ_2: U8.4 (~IRQ), U11.26 (~IRQ)
~NMI: J1.19, J2.19, J14.4, R8.2, U1.6 (~NMI)
~NMI_2: U8.6 (~NMI), U19.1 (~R), U19.8 (~Q), U19.13 (~R)
~RES: D1.2 (A), J14.6, SW1.1, U1.40 (~RESET), U2.1, U11.4 (~RESET), U18.4
~R/W_A: U27.12, U36.6, U45.1 (A->B)
~R/W_B: U27.5, U36.10
~VP_S: J14.7, U8.1 (~VP)

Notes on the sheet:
Debug header pins Addresses, data bus, control stuff
